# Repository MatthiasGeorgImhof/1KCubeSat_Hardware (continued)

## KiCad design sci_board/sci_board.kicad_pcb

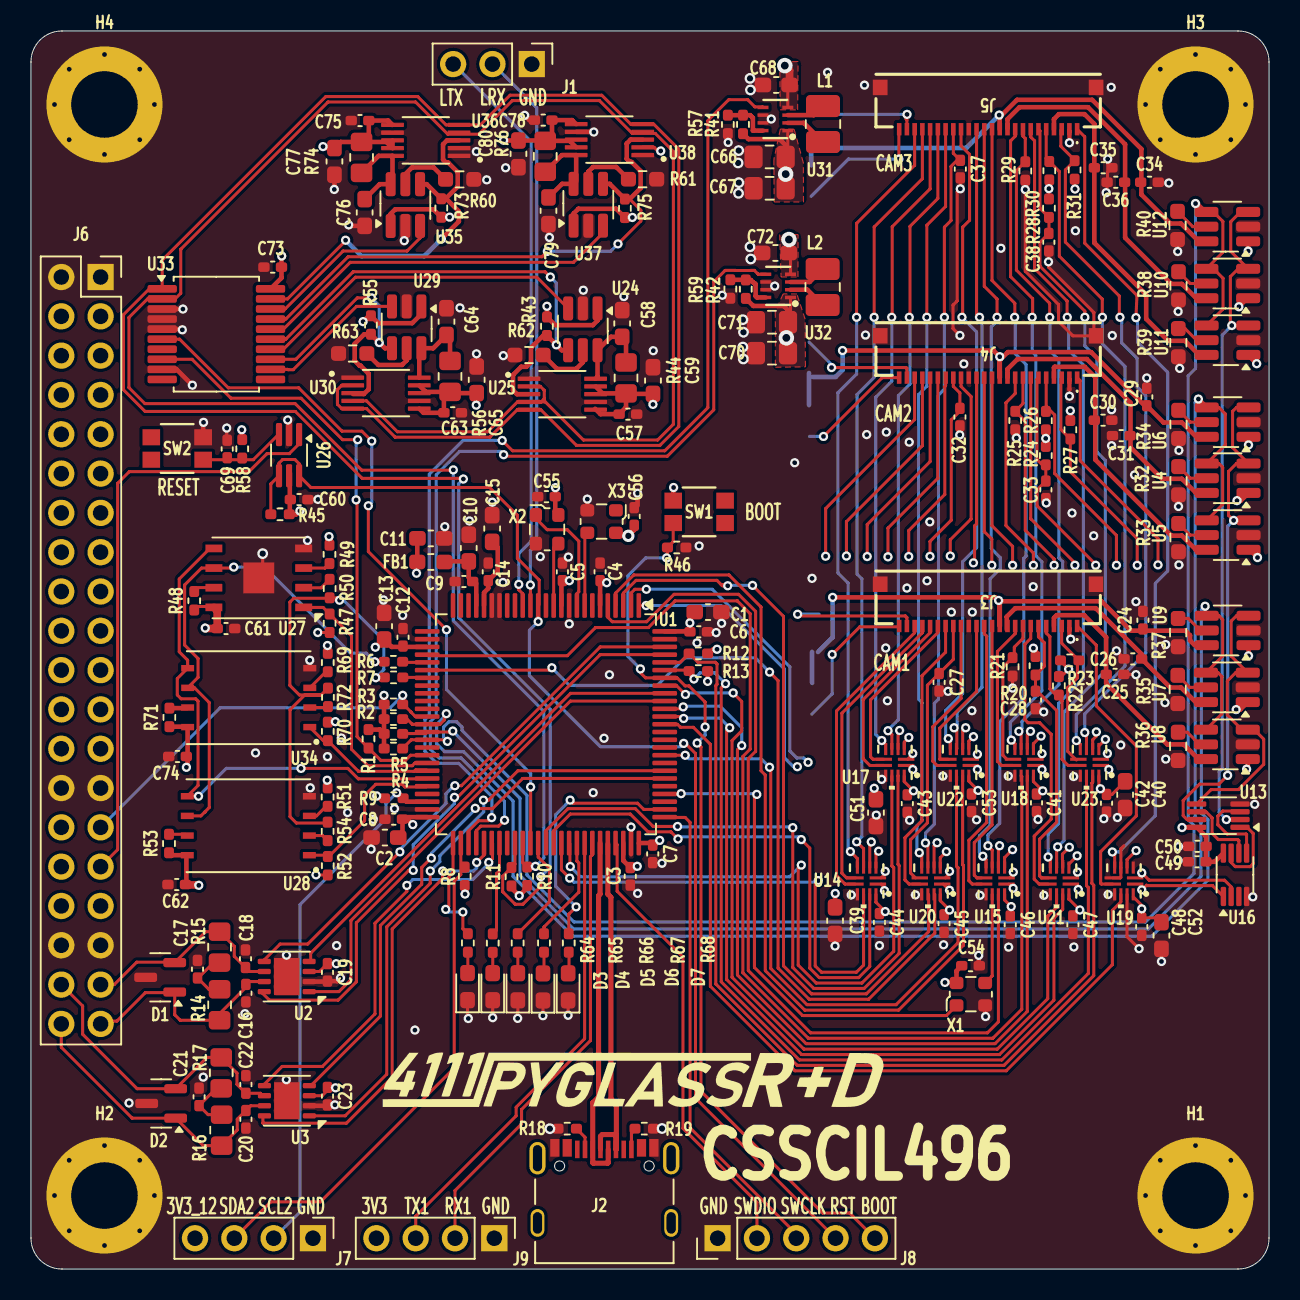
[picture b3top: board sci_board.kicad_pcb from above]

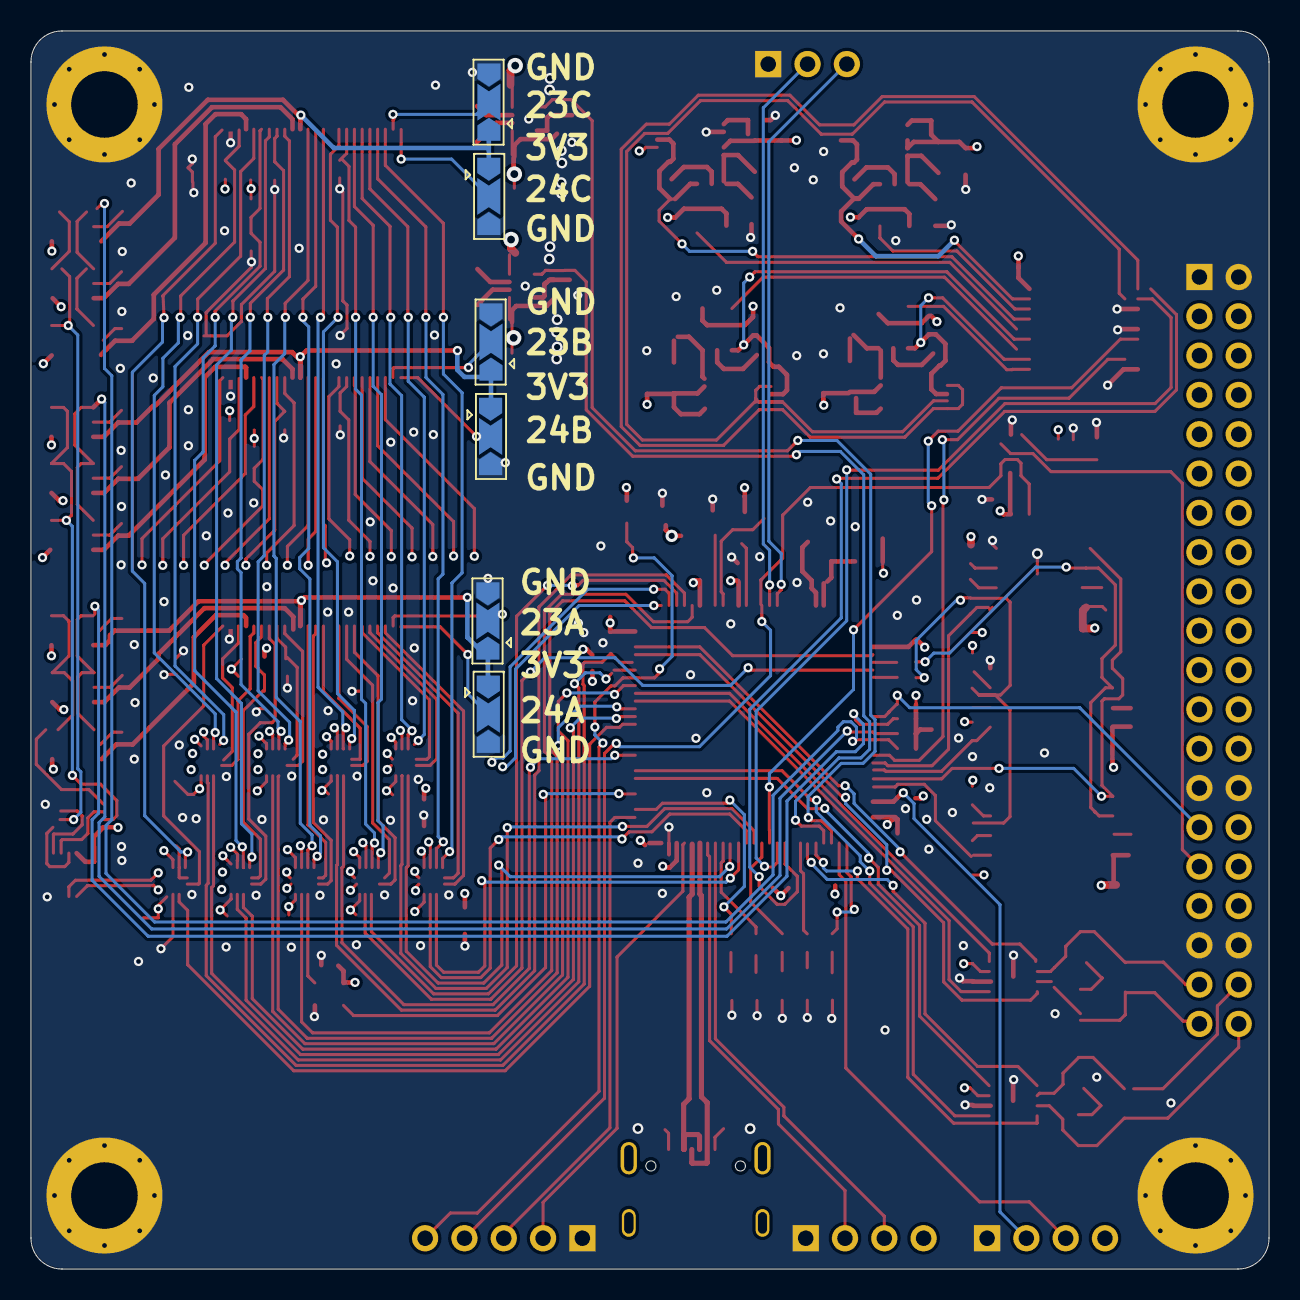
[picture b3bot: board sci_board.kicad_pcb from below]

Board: 4 copper layers, 80.0 x 80.0 mm, 231 parts (6 on the bottom side), 208 nets.

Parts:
C1, C2, C10, C11, C13, C15, C39, C40, C51, C52, C58, C59, C64, C65, C76, C77, C79, C80: 10uF; C_0603_1608Metric_Pad1.08x0.95mm_HandSolder
C3, C4, C5, C6, C7, C8, C9, C12, C14, C19, C23, C24, C25, C26, C28, C29, C30, C31, C33, C34, C35, C36, C38, C41, C42, C43, C44, C45, C46, C47, C48, C49, C50, C53, C54, C55, C56, C57, C60, C61, C62, C63, C69, C73, C74, C75, C78: 100nF; C_0402_1005Metric_Pad0.74x0.62mm_HandSolder
C16, C18, C20, C22: 100pF; C_0402_1005Metric_Pad0.74x0.62mm_HandSolder
C17, C21: 4.7nF; C_0402_1005Metric_Pad0.74x0.62mm_HandSolder
C27, C32, C37: 22pF; C_0402_1005Metric_Pad0.74x0.62mm_HandSolder
C66, C67, C70, C71: 47uF; C_0805_2012Metric_Pad1.18x1.45mm_HandSolder
C68, C72: 22uF; C_0603_1608Metric_Pad1.08x0.95mm_HandSolder
D1, D2: NUP2105LT1G; SOT-23
D3: LED_SMD_RED; LED_0603_1608Metric_Pad1.05x0.95mm_HandSolder
D4: LED_SMD_GREEN; LED_0603_1608Metric_Pad1.05x0.95mm_HandSolder
D5, D6, D7: LED_SMD_YELLOW; LED_0603_1608Metric_Pad1.05x0.95mm_HandSolder
FB1: 120R; L_0603_1608Metric_Pad1.05x0.95mm_HandSolder
H1, H2, H3, H4: MountingHole_Pad; MountingHole_4.3mm_M4_Pad_Via_Custom
J1: Conn_01x03_Pin; PinHeader_1x03_P2.54mm_Vertical
J2: 10155435-00011LF; AMPHENOL_10155435-00011LF
J3, J4, J5: 10051922-2410EHLF; 100519222410EHLF
J6: PC104 Conn_02x20_Odd_Even; PinSocket_2x20_P2.54mm_Vertical
J7: Conn_01x04_Pin; PinHeader_1x04_P2.54mm_Vertical
J8: Conn_01x06; PinHeader_1x05_P2.54mm_Vertical
J9: Conn_01x04; PinHeader_1x04_P2.54mm_Vertical
JP1, JP2, JP3, JP4, JP5, JP6: SolderJumper_3_Open; SolderJumper-3_P2.0mm_Open_TrianglePad1.0x1.5mm
L1, L2: 1uH; L_1008_2520Metric_Pad1.43x2.20mm_HandSolder
NT1, NT2, NT3: NetTie_2; NetTie-2_SMD_Pad0.3mm
R1, R2, R3, R4, R20, R21, R24, R25, R28, R29, R43, R45, R46, R47, R48, R49, R51, R52, R53, R55, R58, R69, R70, R71, R73, R75: 100K; R_0402_1005Metric_Pad0.72x0.64mm_HandSolder
R5: 330K; R_0402_1005Metric_Pad0.72x0.64mm_HandSolder
R6, R7, R50, R54, R72: 22R; R_0402_1005Metric_Pad0.72x0.64mm_HandSolder
R8, R9, R10, R11, R18, R19: 5K1; R_0402_1005Metric_Pad0.72x0.64mm_HandSolder
R12, R13, R22, R23, R26, R27, R30, R31: 10K; R_0402_1005Metric_Pad0.72x0.64mm_HandSolder
R14, R15, R16, R17: 60R4; R_0805_2012Metric_Pad1.20x1.40mm_HandSolder
R32, R33, R34, R35, R36, R37, R38, R39, R40, R60, R61, R62, R63: 988R; R_0603_1608Metric_Pad0.98x0.95mm_HandSolder
R41: 422K; R_0402_1005Metric_Pad0.72x0.64mm_HandSolder
R42: 182K; R_0402_1005Metric_Pad0.72x0.64mm_HandSolder
R44, R56, R74, R76: 10m; R_0805_2012Metric_Pad1.20x1.40mm_HandSolder
R57, R59: 91K; R_0402_1005Metric_Pad0.72x0.64mm_HandSolder
R64, R65, R66, R67, R68: 1K; R_0402_1005Metric_Pad0.72x0.64mm_HandSolder
SW1, SW2: EVP-AA602W; EVP602AA
U1: STM32L496VGTx; LQFP-100_14x14mm_P0.5mm
U2, U3: TCAN3414; VSON-8-1EP_3x3mm_P0.65mm_EP1.65x2.4mm
U4, U5, U6, U7, U8, U9, U10, U11, U12, U24, U29, U35, U37: MIC2009A-1YM6-TR; SOT-23-6_Handsoldering
U13: 74LVC3G04; VSSOP-8_2.3x2mm_P0.5mm
U14, U15, U17, U18, U19, U20, U21, U22, U23: TMUX131RMGR; VQFN12_RMG_TEX
U16: 74LVC1G139; VSSOP-8_2.3x2mm_P0.5mm
U25, U30, U36, U38: INA226AIDGSR; SOP50P490X110-10N
U26: 74LVC2G07; SOT-363_SC-70-6_Handsoldering
U27: MR25H10; DFN-8-1EP_6x5mm_P1.27mm_EP2x2mm
U28, U34: MT29F4G01ABAFDWB-IT:F TR; DFN800X600X65-8N
U31, U32: TPS631000DRLR; TPS631000DRLR_TEX
U33: MCP23008T-E/SS; SSOP-20_5.3x7.2mm_P0.65mm
X1: 24MHz; Oscillator_SMD_ECS_2520MV-xxx-xx-4Pin_2.5x2.0mm
X2: 10MHz; Oscillator_SMD_ECS_2520MV-xxx-xx-4Pin_2.5x2.0mm
X3: 32.768KHZ; Oscillator_SMD_ECS_2520MV-xxx-xx-4Pin_2.5x2.0mm

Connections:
+3V3_AUX: C73.1, J6.12, R43.1, R55.1, R73.1, R75.1, U24.1 (VIN), U29.1 (VIN), U33.20 (VDD), U35.1 (VIN), U37.1 (VIN), U38.2 (A0)
+3V3_STM32_Core: C1.2, C2.2, C3.1, C4.1, C5.1, C6.1, C7.1, C8.1, C11.1, C12.2, C13.2, C19.1, C23.1, C55.1, C56.1, C60.2, FB1.1, J6.17, J9.4, R1.1, R2.1, R3.1, R4.1, R5.1, R8.1, R9.1, R10.1, R11.1, R12.1, R13.1, R45.1, R58.1, SW1.1, U1.6 (VBAT), U1.11 (VDD), U1.28 (VDD), U1.50 (VDD), U1.73 (VDDUSB), U1.75 (VDD), U1.100 (VDD), U2.3 (VCC), U3.3 (VCC), U26.5 (VCC), X2.4 (VDD), X3.4 (VCC)
+BATT: C68.1, C72.1, J6.6, U31.4 (VIN), U32.4 (VIN)
/3V3_Cameras: C39.1, C40.1, C41.1, C42.1, C43.1, C44.1, C45.1, C46.1, C47.1, C48.1, C49.1, C50.1, C51.1, C52.1, C53.1, C54.1, C78.1, C80.1, R76.2, U6.1 (VIN), U9.1 (VIN), U12.1 (VIN), U13.8 (VCC), U14.12 (VDD), U15.12 (VDD), U16.8 (VCC), U17.12 (VDD), U18.12 (VDD), U19.12 (VDD), U20.12 (VDD), U21.12 (VDD), U22.12 (VDD), U23.12 (VDD), U38.6 (VS), U38.8 (VBUS), U38.9 (IN-), X1.4 (VDD)
/3V3_Flash: C57.1, C59.1, C62.1, C74.1, R44.2, R51.1, R52.1, R53.1, R69.1, R70.1, R71.1, U25.6 (VS), U25.8 (VBUS), U25.9 (IN-), U28.8 (VCC), U34.8 (VCC)
/3V3_Imager: C75.1, C77.1, J7.4, R74.2, U36.6 (VS), U36.8 (VBUS), U36.9 (IN-)
/3V3_MRAM: C61.1, C63.1, C65.1, R47.1, R48.1, R49.1, R56.2, U27.8 (VDD), U30.6 (VS), U30.8 (VBUS), U30.9 (IN-)
/ATTN: J6.29, R5.2, U1.37 (PB2)
/Aux Power Switch 3V3/ENABLE0: U33.18 (GP6), U35.3 (ENABLE)
/Aux Power Switch 3V3/ENABLE1: U33.16 (GP4), U37.3 (ENABLE)
/Aux Power Switch 3V3/ENABLE2: U24.3 (ENABLE), U33.14 (GP2)
/Aux Power Switch 3V3/ENABLE3: U29.3 (ENABLE), U33.12 (GP0)
/Aux Power Switch 3V3/INT0: R73.2, U33.19 (GP7), U35.4 (*FAULT), U36.3 (ALERT)
/Aux Power Switch 3V3/INT1: R75.2, U33.17 (GP5), U37.4 (*FAULT), U38.3 (ALERT)
/Aux Power Switch 3V3/INT2: R43.2, U24.4 (*FAULT), U25.3 (ALERT), U33.15 (GP3)
/Aux Power Switch 3V3/INT3: R55.2, U29.4 (*FAULT), U30.3 (ALERT), U33.13 (GP1)
/Aux Power Switch 3V3/RESET: U1.61 (PD14), U33.6 (*RESET)
/Aux Power Switch 3V3/SCL: R11.2, U1.59 (PD12), U25.5 (SCL), U30.2 (A0), U30.5 (SCL), U33.1 (SCL), U36.5 (SCL), U38.5 (SCL)
/Aux Power Switch 3V3/SDA: R10.2, U1.60 (PD13), U25.2 (A0), U25.4 (SDA), U30.4 (SDA), U33.2 (SDA), U36.4 (SDA), U38.4 (SDA)
/Aux Power Switch 3V3/sheet601A160D1/ILIMIT+: R60.1, U35.5 (ILIMIT)
/Aux Power Switch 3V3/sheet601A160D2/ILIMIT+: R61.1, U37.5 (ILIMIT)
/Aux Power Switch 3V3/sheet601A160D3/ILIMIT+: R62.1, U24.5 (ILIMIT)
/Aux Power Switch 3V3/sheet601A160D4/ILIMIT+: R63.1, U29.5 (ILIMIT)
/CAN1_H: C20.1, D2.1 (K), J6.40, R16.1, U3.7 (CANH)
/CAN1_L: C22.2, D2.2 (K), J6.38, R17.2, U3.6 (CANL)
/CAN1_RX: U1.81 (PD0), U3.4 (RXD)
/CAN1_SHDN: U1.56 (PD9), U3.5 (SHTD)
/CAN1_STB: U1.55 (PD8), U3.8 (STB)
/CAN1_TX: U1.82 (PD1), U3.1 (TXD)
/CAN2_H: C16.1, D1.1 (K), J6.39, R14.1, U2.7 (CANH)
/CAN2_L: C18.2, D1.2 (K), J6.37, R15.2, U2.6 (CANL)
/CAN2_RX: U1.92 (PB6), U2.4 (RXD)
/CAN2_SHDN: U1.98 (PE1), U2.5 (SHTD)
/CAN2_STB: U1.97 (PE0), U2.8 (STB)
/CAN2_TX: U1.91 (PB5), U2.1 (TXD)
/Cameras/1V5: C70.1, C71.1, R42.1, U4.1 (VIN), U7.1 (VIN), U10.1 (VIN), U32.1 (VOUT)
/Cameras/1V5_A: C26.1, J3.10, U7.6 (VOUT)
/Cameras/1V5_B: C31.1, J4.10, U4.6 (VOUT)
/Cameras/1V5_C: C36.1, J5.10, U10.6 (VOUT)
/Cameras/2V8: C66.1, C67.1, R41.1, U5.1 (VIN), U8.1 (VIN), U11.1 (VIN), U31.1 (VOUT)
/Cameras/2V8_A: C25.1, J3.4, U8.6 (VOUT)
/Cameras/2V8_B: C30.1, J4.4, U5.6 (VOUT)
/Cameras/2V8_C: C35.1, J5.4, U11.6 (VOUT)
/Cameras/3V3_A: C24.1, J3.11, JP1.1 (A), JP2.1 (A), R20.1, R22.1, R23.1, U9.6 (VOUT)
/Cameras/3V3_B: C29.1, J4.11, JP3.1 (A), JP4.1 (A), R24.1, R26.1, R27.1, U6.6 (VOUT)
/Cameras/3V3_C: C34.1, J5.11, JP5.1 (A), JP6.1 (A), R28.1, R30.1, R31.1, U12.6 (VOUT)
/Cameras/CLK_OE: U1.79 (PC11), X1.1 (TRI-STATE)
/Cameras/Camera_A/*RESET: C28.1, J3.6, R20.2, U21.7 (S1A)
/Cameras/Camera_A/A_GND: J3.2, NT1.1
/Cameras/Camera_A/DCMI_02: J3.19, U17.7 (S1A)
/Cameras/Camera_A/DCMI_03: J3.21, U14.7 (S1A)
/Cameras/Camera_A/DCMI_04: J3.22, U14.8 (S2A)
/Cameras/Camera_A/DCMI_05: J3.20, U17.8 (S2A)
/Cameras/Camera_A/DCMI_06: J3.18, U20.8 (S2A)
/Cameras/Camera_A/DCMI_07: J3.16, U22.8 (S2A)
/Cameras/Camera_A/DCMI_08: J3.14, U22.7 (S1A)
/Cameras/Camera_A/DCMI_09: J3.12, U15.7 (S1A)
/Cameras/Camera_A/DCMI_HSYNC: J3.9, U18.8 (S2A)
/Cameras/Camera_A/DCMI_PLXCLK: C27.1, J3.17, U20.7 (S1A)
/Cameras/Camera_A/DCMI_VSYNC: J3.7, U21.8 (S2A)
/Cameras/Camera_A/PWRDN: J3.8, R21.1, U18.7 (S1A)
/Cameras/Camera_A/SCK: J3.5, R22.2, U23.8 (S2A)
/Cameras/Camera_A/SDA: J3.3, R23.2, U23.7 (S1A)
/Cameras/Camera_A/STROBE: J3.1, U19.8 (S2A)
/Cameras/Camera_A/XCLK: J3.13, U15.8 (S2A)
/Cameras/Camera_B/*RESET: C33.1, J4.6, R24.2, U21.3 (S1B)
/Cameras/Camera_B/A_GND: J4.2, NT2.1
/Cameras/Camera_B/DCMI_02: J4.19, U17.3 (S1B)
/Cameras/Camera_B/DCMI_03: J4.21, U14.3 (S1B)
/Cameras/Camera_B/DCMI_04: J4.22, U14.4 (S2B)
/Cameras/Camera_B/DCMI_05: J4.20, U17.4 (S2B)
/Cameras/Camera_B/DCMI_06: J4.18, U20.4 (S2B)
/Cameras/Camera_B/DCMI_07: J4.16, U22.4 (S2B)
/Cameras/Camera_B/DCMI_08: J4.14, U22.3 (S1B)
/Cameras/Camera_B/DCMI_09: J4.12, U15.3 (S1B)
/Cameras/Camera_B/DCMI_HSYNC: J4.9, U18.4 (S2B)
/Cameras/Camera_B/DCMI_PLXCLK: C32.1, J4.17, U20.3 (S1B)
/Cameras/Camera_B/DCMI_VSYNC: J4.7, U21.4 (S2B)
/Cameras/Camera_B/PWRDN: J4.8, R25.1, U18.3 (S1B)
/Cameras/Camera_B/SCK: J4.5, R26.2, U23.4 (S2B)
/Cameras/Camera_B/SDA: J4.3, R27.2, U23.3 (S1B)
/Cameras/Camera_B/STROBE: J4.1, U19.4 (S2B)
/Cameras/Camera_B/XCLK: J4.13, U15.4 (S2B)
/Cameras/Camera_C/*RESET: C38.1, J5.6, R28.2, U21.5 (S1C)
/Cameras/Camera_C/A_GND: J5.2, NT3.1
/Cameras/Camera_C/DCMI_02: J5.19, U17.5 (S1C)
/Cameras/Camera_C/DCMI_03: J5.21, U14.5 (S1C)
/Cameras/Camera_C/DCMI_04: J5.22, U14.6 (S2C)
/Cameras/Camera_C/DCMI_05: J5.20, U17.6 (S2C)
/Cameras/Camera_C/DCMI_06: J5.18, U20.6 (S2C)
/Cameras/Camera_C/DCMI_07: J5.16, U22.6 (S2C)
/Cameras/Camera_C/DCMI_08: J5.14, U22.5 (S1C)
/Cameras/Camera_C/DCMI_09: J5.12, U15.5 (S1C)
/Cameras/Camera_C/DCMI_HSYNC: J5.9, U18.6 (S2C)
/Cameras/Camera_C/DCMI_PLXCLK: C37.1, J5.17, U20.5 (S1C)
/Cameras/Camera_C/DCMI_VSYNC: J5.7, U21.6 (S2C)
/Cameras/Camera_C/PWRDN: J5.8, R29.1, U18.5 (S1C)
/Cameras/Camera_C/SCK: J5.5, R30.2, U23.6 (S2C)
/Cameras/Camera_C/SDA: J5.3, R31.2, U23.5 (S1C)
/Cameras/Camera_C/STROBE: J5.1, U19.6 (S2C)
/Cameras/Camera_C/XCLK: J5.13, U15.6 (S2C)
/Cameras/DCMI_00: U1.63 (PC6), U17.11 (D1)
/Cameras/DCMI_01: U1.64 (PC7), U14.11 (D1)
/Cameras/DCMI_02: U1.65 (PC8), U14.10 (D2)
/Cameras/DCMI_03: U1.66 (PC9), U17.10 (D2)
/Cameras/DCMI_04: U1.3 (PE4), U20.10 (D2)
/Cameras/DCMI_05: U1.84 (PD3), U22.10 (D2)
/Cameras/DCMI_06: U1.4 (PE5), U22.11 (D1)
/Cameras/DCMI_07: U1.5 (PE6), U15.11 (D1)
/Cameras/DCMI_HSYNC: U1.29 (PA4), U18.10 (D2)
/Cameras/DCMI_PLXCLK: U1.31 (PA6), U20.11 (D1)
/Cameras/DCMI_VSYNC: U1.93 (PB7), U21.10 (D2)
/Cameras/EN_1V5: U1.54 (PB15), U32.5 (EN)
/Cameras/EN_2V8: U1.53 (PB14), U31.5 (EN)
/Cameras/I2C_SCK: R13.2, U1.95 (PB8), U23.10 (D2)
/Cameras/I2C_SDA: R12.2, U1.96 (PB9), U23.11 (D1)
/Cameras/Multiplexer/EN_A: U7.3 (ENABLE), U8.3 (ENABLE), U9.3 (ENABLE), U13.5
/Cameras/Multiplexer/EN_B: U4.3 (ENABLE), U5.3 (ENABLE), U6.3 (ENABLE), U13.7
/Cameras/Multiplexer/EN_C: U10.3 (ENABLE), U11.3 (ENABLE), U12.3 (ENABLE), U13.2
/Cameras/PWRDN: U1.90 (PB4), U18.11 (D1)
/Cameras/Power Regulator MP3416/LX1: L1.2, U31.3 (LX1)
/Cameras/Power Regulator MP3416/LX2: L1.1, U31.2 (LX2)
/Cameras/Power Regulator MP3416/R-: R41.2, R57.1, U31.8 (FB)
/Cameras/Power Regulator MP3417/LX1: L2.2, U32.3 (LX1)
/Cameras/Power Regulator MP3417/LX2: L2.1, U32.2 (LX2)
/Cameras/Power Regulator MP3417/R-: R42.2, R59.1, U32.8 (FB)
/Cameras/RESET: U1.89 (PB3), U21.11 (D1)
/Cameras/S0: U1.1 (PE2), U14.1 (SEL0), U15.1 (SEL0), U16.1 (A), U17.1 (SEL0), U18.1 (SEL0), U19.1 (SEL0), U20.1 (SEL0), U21.1 (SEL0), U22.1 (SEL0), U23.1 (SEL0)
/Cameras/S1: U1.2 (PE3), U14.2 (SEL1), U15.2 (SEL1), U16.2 (B), U17.2 (SEL1), U18.2 (SEL1), U19.2 (SEL1), U20.2 (SEL1), U21.2 (SEL1), U22.2 (SEL1), U23.2 (SEL1)
/Cameras/STROBE: U1.88 (PD7), U19.10 (D2)
/Cameras/XCLK: U15.10 (D2), X1.3 (OUTPUT)
/Flash1/SPI_CLK: R6.2, U27.6 (SCK), U28.6 (SCK), U34.6 (SCK)
/Flash1/SPI_CS: R52.2, U1.46 (PE15), U28.1 (CS#)
/Flash1/SPI_MISO: R7.2, R50.2, R54.1, R72.1
/Flash1/SPI_MOSI: U1.45 (PE14), U27.5 (SI), U28.5 (SI/IO0), U34.5 (SI/IO0)
/Flash2/SPI_CS: R70.2, U1.44 (PE13), U34.1 (CS#)
/INT1: R2.2, U1.38 (PE7), U7.4 (*FAULT), U8.4 (*FAULT), U9.4 (*FAULT)
/INT2: R3.2, U1.39 (PE8), U4.4 (*FAULT), U5.4 (*FAULT), U6.4 (*FAULT)
/INT3: R4.2, U1.40 (PE9), U10.4 (*FAULT), U11.4 (*FAULT), U12.4 (*FAULT)
/MRAM/SPI_CS: R47.2, U1.43 (PE12), U27.1 (~CS)
/PMIC/BOOT0: J8.5, R46.1, SW1.2, U1.94 (PH3)
/PMIC/I2C2_SCK: J7.2, R9.2, U1.48 (PB11)
/PMIC/I2C2_SDA: J7.3, R8.2, U1.52 (PB13)
/PMIC/LED1: R64.1, U1.51 (PB12)
/PMIC/LED2: R65.1, U1.57 (PD10)
/PMIC/LED3: R66.1, U1.62 (PD15)
/PMIC/LED4: R67.1, U1.67 (PA8)
/PMIC/LED5: R68.1, U1.77 (PA15)
/PMIC/LPUART_RX: J1.2, U1.15 (PC0)
/PMIC/LPUART_TX: J1.3, U1.16 (PC1)
/PMIC/OSC32_TCXO/OUT: U1.8 (PC14), X3.3 (OUT)
/PMIC/OSC_HSE_OE: U1.9 (PC15), X2.1 (TRI-STATE)
/PMIC/OSC_HSE_TCXO/OUT: U1.12 (PH0), X2.3 (OUTPUT)
/PMIC/RESET: J8.4, R45.2, U1.14 (NRST), U26.4 (OUT2), U26.6 (OUT1)
/PMIC/RESET/RESET: C69.1, R58.2, SW2.3, U26.3 (IN2)
/PMIC/SWCLK: J8.3, U1.76 (PA14)
/PMIC/SWDIO: J8.2, U1.72 (PA13)
/PMIC/USART1_RX: J9.2, U1.69 (PA10)
/PMIC/USART1_TX: J9.3, U1.68 (PA9)
/PMIC/USB_OTG_FS_DM: J2.A7 (DN1_A), J2.B7 (DN2_B), U1.70 (PA11)
/PMIC/USB_OTG_FS_DP: J2.A6 (DP1_A), J2.B6 (DP2_B), U1.71 (PA12)
/Power_INT: R1.2, U1.42 (PE11), U33.8 (INT)
/RESET: J6.31, U26.1 (IN1)
GND: C1.1, C2.1, C3.2, C4.2, C5.2, C6.2, C7.2, C8.2, C9.2, C10.2, C11.2, C12.1, C13.1, C14.1, C15.1, C16.2, C17.2, C18.1, C19.2, C20.2, C21.2, C22.1, C23.2, C24.2, C25.2, C26.2, C27.2, C28.2, C29.2, C30.2, C31.2, C32.2, C33.2, C34.2, C35.2, C36.2, C37.2, C38.2, C39.2, C40.2, C41.2, C42.2, C43.2, C44.2, C45.2, C46.2, C47.2, C48.2, C49.2, C50.2, C51.2, C52.2, C53.2, C54.2, C55.2, C56.2, C57.2, C58.2, C59.2, C60.1, C61.2, C62.2, C63.2, C64.2, C65.2, C66.2, C67.2, C68.2, C69.2, C70.2, C71.2, C72.2, C73.2, C74.2, C75.2, C76.2, C77.2, C78.2, C79.2, C80.2, D1.3 (A), D2.3 (A), D3.1 (K), D4.1 (K), D5.1 (K), D6.1 (K), D7.1 (K), H1.1, H2.1, H3.1, H4.1, J1.1, J2.A1_B12 (GND), J2.B1_A12 (GND__1), J3.15, J3.MP1, J3.MP2, J4.15, J4.MP1, J4.MP2, J5.15, J5.MP1, J5.MP2, J6.1, J6.2, J6.27, J6.28, J6.35, J6.36, J7.1, J8.1, J9.1, JP1.3 (B), JP2.3 (B), JP3.3 (B), JP4.3 (B), JP5.3 (B), JP6.3 (B), NT1.2, NT2.2, NT3.2, R18.1, R19.1, R21.2, R25.2, R29.2, R32.2, R33.2, R34.2, R35.2, R36.2, R37.2, R38.2, R39.2, R40.2, R46.2, R57.2, R59.2, R60.2, R61.2, R62.2, R63.2, SW2.4, U1.10 (VSS), U1.19 (VSSA), U1.20 (VREF-), U1.27 (VSS), U1.49 (VSS), U1.74 (VSS), U1.99 (VSS), U2.2 (GND), U2.9 (GND), U3.2 (GND), U3.9 (GND), U4.2 (GND), U5.2 (GND), U6.2 (GND), U7.2 (GND), U8.2 (GND), U9.2 (GND), U10.2 (GND), U11.2 (GND), U12.2 (GND), U13.4 (GND), U14.9 (GND), U15.9 (GND), U16.4 (GND), U17.9 (GND), U18.9 (GND), U19.3 (S1B), U19.5 (S1C), U19.7 (S1A), U19.9 (GND), U19.11 (D1), U20.9 (GND), U21.9 (GND), U22.9 (GND), U23.9 (GND), U24.2 (GND), U25.1 (A1), U25.7 (GND), U26.2 (GND), U27.4 (VSS), U27.9 (PAD), U28.4 (VSS), U29.2 (GND), U30.1 (A1), U30.7 (GND), U31.6 (MODE), U31.7 (GND), U32.6 (MODE), U32.7 (GND), U33.3 (A2), U33.4 (A1), U33.5 (A0), U33.9 (VSS), U34.4 (VSS), U35.2 (GND), U36.1 (A1), U36.2 (A0), U36.7 (GND), U37.2 (GND), U38.1 (A1), U38.7 (GND), X1.2 (GND), X2.2 (GND), X3.2 (GND)
unnamed: C17.1, R14.2, R15.1
unnamed: C21.1, R16.2, R17.1
unnamed: D3.2 (A), R64.2
unnamed: D4.2 (A), R65.2
unnamed: D5.2 (A), R66.2
unnamed: D6.2 (A), R67.2
unnamed: D7.2 (A), R68.2
unnamed: J2.A5 (CC1_A), R18.2
unnamed: J2.B5 (CC2_B), R19.2
unnamed: J3.23, JP1.2 (C)
unnamed: J3.24, JP2.2 (C)
unnamed: J4.23, JP3.2 (C)
unnamed: J4.24, JP4.2 (C)
unnamed: J5.23, JP5.2 (C)
unnamed: J5.24, JP6.2 (C)
unnamed: R6.1, U1.30 (PA5)
unnamed: R7.1, U1.32 (PA7)
unnamed: C9.1, C10.1, FB1.2, U1.22 (VDDA)
unnamed: C14.2, C15.2, U1.21 (VREF+)
unnamed: R32.1, U4.5 (ILIMIT)
unnamed: R33.1, U5.5 (ILIMIT)
unnamed: R34.1, U6.5 (ILIMIT)
unnamed: R35.1, U7.5 (ILIMIT)
unnamed: R36.1, U8.5 (ILIMIT)
unnamed: R37.1, U9.5 (ILIMIT)
unnamed: R38.1, U10.5 (ILIMIT)
unnamed: R39.1, U11.5 (ILIMIT)
unnamed: R40.1, U12.5 (ILIMIT)
unnamed: U13.1, U16.7 (Y0)
unnamed: U13.6, U16.6 (Y1)
unnamed: U13.3, U16.5 (Y2)
unnamed: C58.1, R44.1, U24.6 (VOUT), U25.10 (IN+)
unnamed: R50.1, U27.2 (SO)
unnamed: R48.2, U27.7 (~HOLD)
unnamed: R49.2, U27.3 (~WP)
unnamed: R53.2, U28.7 (HOLD#/IO3)
unnamed: R54.2, U28.2 (SO/IO1)
unnamed: R51.2, U28.3 (WP#/IO2)
unnamed: C64.1, R56.1, U29.6 (VOUT), U30.10 (IN+)
unnamed: R71.2, U34.7 (HOLD#/IO3)
unnamed: R72.2, U34.2 (SO/IO1)
unnamed: R69.2, U34.3 (WP#/IO2)
unnamed: C76.1, R74.1, U35.6 (VOUT), U36.10 (IN+)
unnamed: C79.1, R76.1, U37.6 (VOUT), U38.10 (IN+)

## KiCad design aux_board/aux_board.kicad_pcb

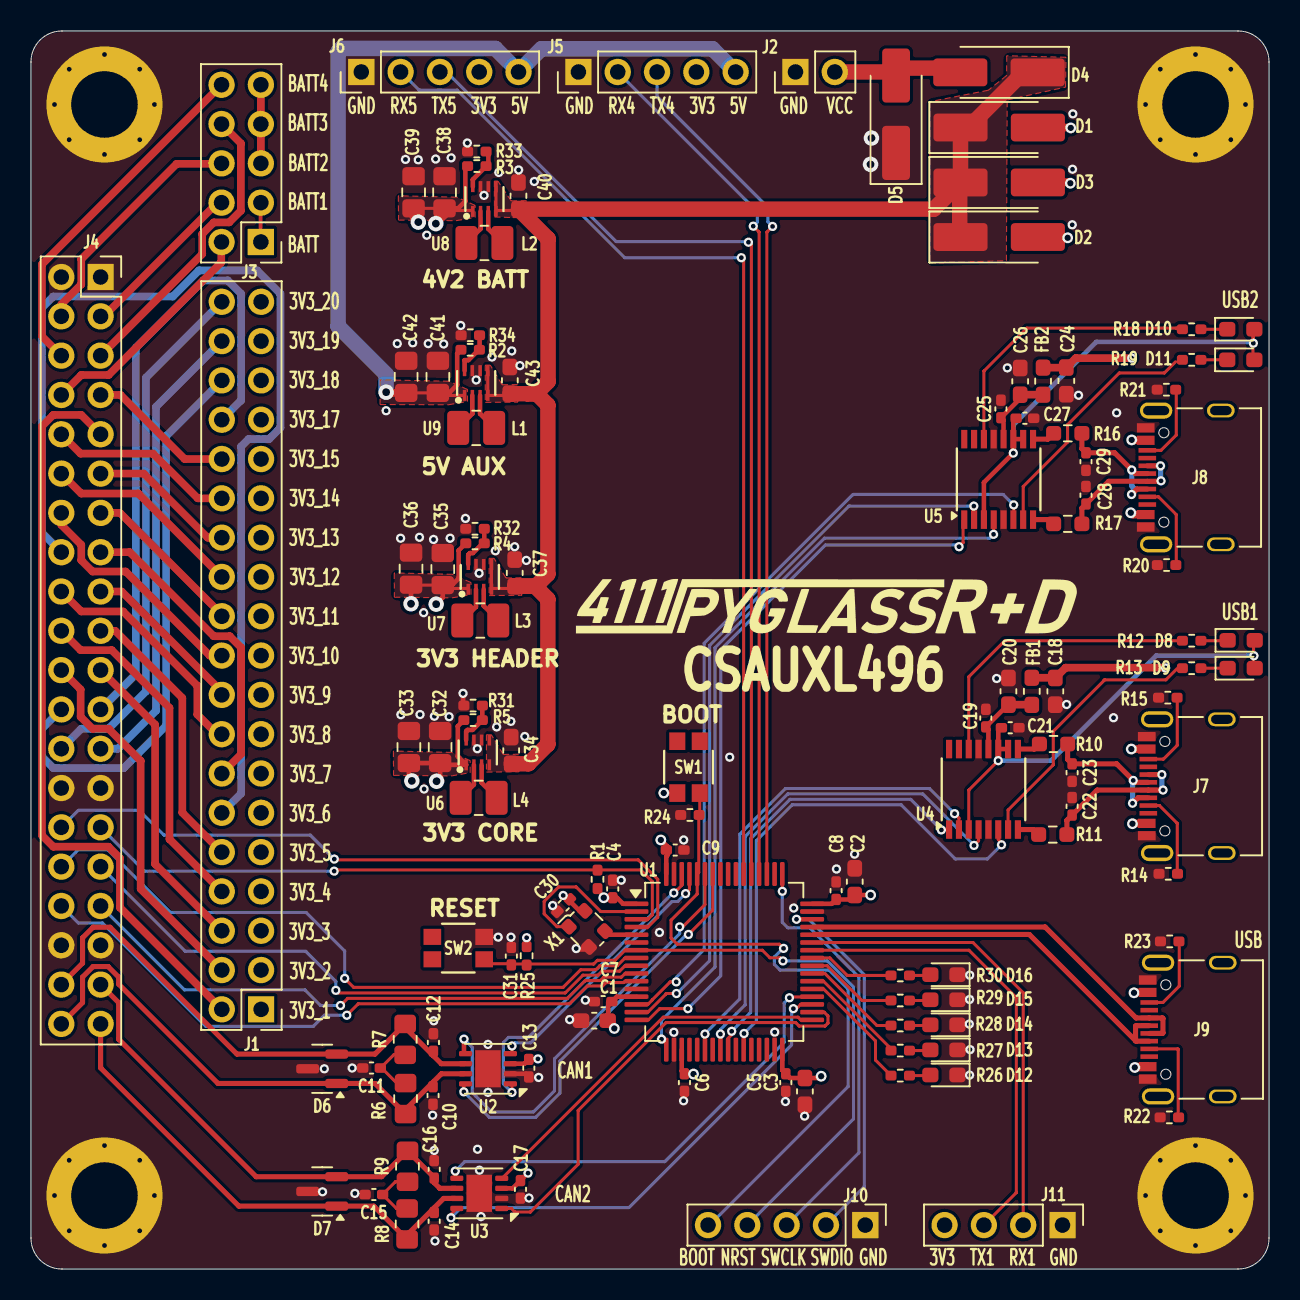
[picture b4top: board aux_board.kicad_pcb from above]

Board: 4 copper layers, 80.0 x 80.0 mm, 126 parts (0 on the bottom side), 124 nets.

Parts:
C1, C2, C3, C18, C20, C24, C26: 10uF; C_0603_1608Metric_Pad1.08x0.95mm_HandSolder
C4, C5, C6, C7, C8, C9, C13, C17, C19, C21, C25, C27, C30, C31: 100nF; C_0402_1005Metric_Pad0.74x0.62mm_HandSolder
C10, C12, C14, C16: 100pF; C_0402_1005Metric_Pad0.74x0.62mm_HandSolder
C11, C15: 4.7nF; C_0402_1005Metric_Pad0.74x0.62mm_HandSolder
C22, C23, C28, C29: 47pF; C_0402_1005Metric_Pad0.74x0.62mm_HandSolder
C32, C33, C35, C36, C38, C39, C41, C42: 47uF; C_0805_2012Metric_Pad1.18x1.45mm_HandSolder
C34, C37, C40, C43: 22uF; C_0603_1608Metric_Pad1.08x0.95mm_HandSolder
D1, D2, D3, D4: CDBA240LL-HF; D_SMA_Handsoldering
D5: SMAJ5.0A; D_SMA_Handsoldering
D6, D7: NUP2105LT1G; SOT-23
D8, D10, D13: LED_SMD_GREEN; LED_0603_1608Metric_Pad1.05x0.95mm_HandSolder
D9, D11, D12: LED_SMD_RED; LED_0603_1608Metric_Pad1.05x0.95mm_HandSolder
D14, D15, D16: LED_SMD_YELLOW; LED_0603_1608Metric_Pad1.05x0.95mm_HandSolder
FB1, FB2: 120R; L_0603_1608Metric_Pad1.05x0.95mm_HandSolder
H1, H2, H3, H4: MountingHole_Pad; MountingHole_4.3mm_M4_Pad_Via_Custom
J1: Conn_02x19_Odd_Even; PinHeader_2x19_P2.54mm_Vertical
J2: Conn_01x02_Pin; PinHeader_1x02_P2.54mm_Vertical
J3: Conn_02x05_Odd_Even; PinHeader_2x05_P2.54mm_Vertical
J4: PC104 Conn_02x20_Odd_Even; PinSocket_2x20_P2.54mm_Vertical
J5, J6: Conn_01x05_Pin; PinHeader_1x05_P2.54mm_Vertical
J7, J8, J9: 10155435-00011LF; AMPHENOL_10155435-00011LF
J10: Conn_01x06; PinHeader_1x05_P2.54mm_Vertical
J11: Conn_01x04; PinHeader_1x04_P2.54mm_Vertical
L1, L2, L3, L4: 1uH; L_1008_2520Metric_Pad1.43x2.20mm_HandSolder
R1: 330K; R_0402_1005Metric_Pad0.72x0.64mm_HandSolder
R2: 806K; R_0402_1005Metric_Pad0.72x0.64mm_HandSolder
R3: 665K; R_0402_1005Metric_Pad0.72x0.64mm_HandSolder
R4, R5: 511K; R_0402_1005Metric_Pad0.72x0.64mm_HandSolder
R6, R7, R8, R9: 60R4; R_0805_2012Metric_Pad1.20x1.40mm_HandSolder
R10, R11, R16, R17: 27R; R_0603_1608Metric_Pad0.98x0.95mm_HandSolder
R12, R13, R18, R19, R26, R27, R28, R29, R30: 1K; R_0402_1005Metric_Pad0.72x0.64mm_HandSolder
R14, R15, R20, R21, R22, R23: 5K1; R_0402_1005Metric_Pad0.72x0.64mm_HandSolder
R24, R25: 100K; R_0402_1005Metric_Pad0.72x0.64mm_HandSolder
R31, R32, R33, R34: 91K; R_0402_1005Metric_Pad0.72x0.64mm_HandSolder
SW1, SW2: EVP-AA602W; EVP602AA
U1: STM32L496RGT6; LQFP-64_10x10mm_P0.5mm
U2, U3: TCAN3414; VSON-8-1EP_3x3mm_P0.65mm_EP1.65x2.4mm
U4, U5: FT230XS; SSOP-16_3.9x4.9mm_P0.635mm
U6, U7, U8, U9: TPS631000DRLR; TPS631000DRLR_TEX
X1: 10MHz; Oscillator_SMD_ECS_2520MV-xxx-xx-4Pin_2.5x2.0mm

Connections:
+3V3: C35.1, C36.1, J1.1, J1.3, J1.5, J1.7, J1.9, J1.11, J1.13, J1.15, J1.17, J1.19, J1.21, J1.23, J1.25, J1.27, J1.29, J1.31, J1.33, J1.35, J1.37, R4.2, U7.1 (VOUT)
+3V3_Core: C1.1, C2.1, C3.1, C4.1, C5.1, C6.1, C7.1, C8.1, C9.1, C13.1, C17.1, C30.1, C32.1, C33.1, J5.4, J6.4, J11.4, R1.1, R5.2, R25.1, SW1.1, U1.1 (VBAT), U1.13 (VDDA), U1.19 (VDD), U1.32 (VDD), U1.48 (VDDUSB), U1.64 (VDD), U2.3 (VCC), U3.3 (VCC), U6.1 (VOUT), X1.4 (VDD)
+5V: C41.1, C42.1, J5.5, J6.5, R2.2, U9.1 (VOUT)
+VBAT: C38.1, C39.1, J3.1, J3.3, J3.5, J3.7, J3.9, R3.2, U8.1 (VOUT)
/*ATTENTION: J4.29, R1.2, U1.3 (PC14)
/*AVI_RST: J4.32, U1.8 (PC0)
/*COMM1_RST: J4.33, U1.10 (PC2)
/*COMM2_RST: J4.34, U1.11 (PC3)
/*EPS_RST: J4.30, U1.4 (PC15)
/*SCI_RST: J4.31, U1.9 (PC1)
/CAN1_H: C10.1, D6.1 (K), J4.40, R6.1, U2.7 (CANH)
/CAN1_L: C12.2, D6.2 (K), J4.38, R7.2, U2.6 (CANL)
/CAN2_H: C14.1, D7.1 (K), J4.39, R8.1, U3.7 (CANH)
/CAN2_L: C16.2, D7.2 (K), J4.37, R9.2, U3.6 (CANL)
/CAN TO USB/BOOT: J10.5, R24.1, SW1.2, U1.60 (PH3_BOOT0)
/CAN TO USB/CAN1_RX: U1.61 (PB8), U2.4 (RXD)
/CAN TO USB/CAN1_SHTD: U1.59 (PB7), U2.5 (SHTD)
/CAN TO USB/CAN1_STB: U1.58 (PB6), U2.8 (STB)
/CAN TO USB/CAN1_TX: U1.62 (PB9), U2.1 (TXD)
/CAN TO USB/CAN2_RX: U1.33 (PB12), U3.4 (RXD)
/CAN TO USB/CAN2_SHTD: U1.36 (PB15), U3.5 (SHTD)
/CAN TO USB/CAN2_STB: U1.35 (PB14), U3.8 (STB)
/CAN TO USB/CAN2_TX: U1.34 (PB13), U3.1 (TXD)
/CAN TO USB/FTDI1/3V3: C27.1, D10.2 (A), D11.2 (A), U5.3 (VCCIO), U5.10 (3V3OUT), U5.11 (~RESET)
/CAN TO USB/FTDI1/RXLED: R19.2, U5.7 (CBUS2)
/CAN TO USB/FTDI1/TXLED: R18.2, U5.14 (CBUS1)
/CAN TO USB/FTDI1/USB/DN: C29.1, J8.A7 (DN1_A), J8.B7 (DN2_B), R16.1
/CAN TO USB/FTDI1/USB/DP: C28.1, J8.A6 (DP1_A), J8.B6 (DP2_B), R17.1
/CAN TO USB/FTDI/3V3: C21.1, D8.2 (A), D9.2 (A), U4.3 (VCCIO), U4.10 (3V3OUT), U4.11 (~RESET)
/CAN TO USB/FTDI/RXLED: R13.2, U4.7 (CBUS2)
/CAN TO USB/FTDI/TXLED: R12.2, U4.14 (CBUS1)
/CAN TO USB/FTDI/USB/DN: C23.1, J7.A7 (DN1_A), J7.B7 (DN2_B), R10.1
/CAN TO USB/FTDI/USB/DP: C22.1, J7.A6 (DP1_A), J7.B6 (DP2_B), R11.1
/CAN TO USB/HSE_IN: U1.5 (PH0), X1.3 (OUTPUT)
/CAN TO USB/LED1: R26.1, U1.37 (PC6)
/CAN TO USB/LED2: R27.1, U1.38 (PC7)
/CAN TO USB/LED3: R28.1, U1.39 (PC8)
/CAN TO USB/LED4: R29.1, U1.40 (PC9)
/CAN TO USB/LED5: R30.1, U1.41 (PA8)
/CAN TO USB/NRST: C31.1, J10.4, R25.2, SW2.3, U1.7 (NRST)
/CAN TO USB/OSC_HSE_OE: U1.2 (PC13), X1.1 (TRI-STATE)
/CAN TO USB/SYS_JTMS_SWCLK: J10.3, U1.49 (PA14)
/CAN TO USB/SYS_JTMS_SWDIO: J10.2, U1.46 (PA13)
/CAN TO USB/UART4_RX: J5.2, U1.52 (PC11)
/CAN TO USB/UART4_TX: J5.3, U1.51 (PC10)
/CAN TO USB/UART5_RX: J6.2, U1.54 (PD2)
/CAN TO USB/UART5_TX: J6.3, U1.53 (PC12)
/CAN TO USB/USART1_RX: J11.2, U1.43 (PA10)
/CAN TO USB/USART1_TX: J11.3, U1.42 (PA9)
/CAN TO USB/USART2_CTS: U1.14 (PA0), U5.6 (~CTS)
/CAN TO USB/USART2_RTS: U1.15 (PA1), U5.2 (~RTS)
/CAN TO USB/USART2_RX: U1.17 (PA3), U5.4 (RXD)
/CAN TO USB/USART2_TX: U1.16 (PA2), U5.1 (TXD)
/CAN TO USB/USART3_CTS: U1.22 (PA6), U4.2 (~RTS)
/CAN TO USB/USART3_RTS: U1.27 (PB1), U4.6 (~CTS)
/CAN TO USB/USART3_RX: U1.25 (PC5), U4.1 (TXD)
/CAN TO USB/USART3_TX: U1.24 (PC4), U4.4 (RXD)
/CAN TO USB/USB_OTG_FS_D+: J9.A6 (DP1_A), J9.B6 (DP2_B), U1.45 (PA12)
/CAN TO USB/USB_OTG_FS_D-: J9.A7 (DN1_A), J9.B7 (DN2_B), U1.44 (PA11)
/CAN TO USB/VBUS1: D1.2 (A), J9.A4_B9 (VBUS), J9.B4_A9 (VBUS__1)
/CAN TO USB/VBUS2: C24.1, D2.2 (A), FB2.1, J8.A4_B9 (VBUS), J8.B4_A9 (VBUS__1)
/CAN TO USB/VBUS3: C18.1, D3.2 (A), FB1.1, J7.A4_B9 (VBUS), J7.B4_A9 (VBUS__1)
/INTERBOARD_CONNECTOR/3V3_1_AVI_STM_CORE: J1.2, J4.9
/INTERBOARD_CONNECTOR/3V3_2_AVI_GPS: J1.4, J4.22
/INTERBOARD_CONNECTOR/3V3_3_AVI_MRAM: J1.6, J4.21
/INTERBOARD_CONNECTOR/3V3_4_AVI_SUN: J1.8, J4.20
/INTERBOARD_CONNECTOR/3V3_5_AVI_ACS_LOGIC: J1.10, J4.19
/INTERBOARD_CONNECTOR/3V3_6_AVI_GYRO: J1.12, J4.16
/INTERBOARD_CONNECTOR/3V3_7_AVI_MAG: J1.14, J4.15
/INTERBOARD_CONNECTOR/3V3_8_AVI_CLK: J1.16, J4.18
/INTERBOARD_CONNECTOR/3V3_9_SCI_STM_CORE: J1.18, J4.17
/INTERBOARD_CONNECTOR/3V3_10_SCI_MRAM: J1.20, J4.14
/INTERBOARD_CONNECTOR/3V3_11_SCI_FLASH: J1.22, J4.13
/INTERBOARD_CONNECTOR/3V3_12_SCI_THERMAL: J1.24, J4.12
/INTERBOARD_CONNECTOR/3V3_13_SCI_CAMERAS: J1.26, J4.11
/INTERBOARD_CONNECTOR/3V3_14_EXTRA1: J1.28, J4.10
/INTERBOARD_CONNECTOR/3V3_15_EXTRA2: J1.30, J4.7
/INTERBOARD_CONNECTOR/3V3_17_RF1_BRIDGE: J1.32, J4.23
/INTERBOARD_CONNECTOR/3V3_18_RF1_COMM: J1.34, J4.24
/INTERBOARD_CONNECTOR/3V3_19_RF2_BRIDGE: J1.36, J4.25
/INTERBOARD_CONNECTOR/3V3_20_RF2_COMM: J1.38, J4.26
/INTERBOARD_CONNECTOR/BATT: J3.2, J4.8
/INTERBOARD_CONNECTOR/BATT_1_COMM1_VRF: J3.4, J4.3
/INTERBOARD_CONNECTOR/BATT_2_COMM2_VRF: J3.6, J4.4
/INTERBOARD_CONNECTOR/BATT_3_AVI_ACS_COIL: J3.8, J4.5
/INTERBOARD_CONNECTOR/BATT_4_SCI_CAMERAS: J3.10, J4.6
/Regulator 3V3/LX1: L3.1, U7.3 (LX1)
/Regulator 3V3/LX2: L3.2, U7.2 (LX2)
/Regulator 3V3/R-: R4.1, R32.1, U7.8 (FB)
/Regulator 3V4/LX1: L4.1, U6.3 (LX1)
/Regulator 3V4/LX2: L4.2, U6.2 (LX2)
/Regulator 3V4/R-: R5.1, R31.1, U6.8 (FB)
/Regulator 4V2/LX1: L2.1, U8.3 (LX1)
/Regulator 4V2/LX2: L2.2, U8.2 (LX2)
/Regulator 4V2/R-: R3.1, R33.1, U8.8 (FB)
/Regulator 5V/LX1: L1.1, U9.3 (LX1)
/Regulator 5V/LX2: L1.2, U9.2 (LX2)
/Regulator 5V/R-: R2.1, R34.1, U9.8 (FB)
GND: C1.2, C2.2, C3.2, C4.2, C5.2, C6.2, C7.2, C8.2, C9.2, C10.2, C11.2, C12.1, C13.2, C14.2, C15.2, C16.1, C17.2, C18.2, C19.2, C20.2, C21.2, C22.2, C23.2, C24.2, C25.2, C26.2, C27.2, C28.2, C29.2, C30.2, C31.2, C32.2, C33.2, C34.2, C35.2, C36.2, C37.2, C38.2, C39.2, C40.2, C41.2, C42.2, C43.2, D5.1 (A1), D6.3 (A), D7.3 (A), D12.1 (K), D13.1 (K), D14.1 (K), D15.1 (K), D16.1 (K), H1.1, H2.1, H3.1, H4.1, J2.1, J4.1, J4.2, J4.27, J4.28, J4.35, J4.36, J5.1, J6.1, J7.A1_B12 (GND), J7.B1_A12 (GND__1), J8.A1_B12 (GND), J8.B1_A12 (GND__1), J9.A1_B12 (GND), J9.B1_A12 (GND__1), J10.1, J11.1, R14.1, R15.1, R20.1, R21.1, R22.1, R23.1, R24.2, R31.2, R32.2, R33.2, R34.2, SW2.4, U1.12 (VSSA), U1.18 (VSS), U1.31 (VSS), U1.47 (VSS), U1.63 (VSS), U2.2 (GND), U2.9 (GND), U3.2 (GND), U3.9 (GND), U4.5 (GND), U4.13 (GND), U5.5 (GND), U5.13 (GND), U6.6 (MODE), U6.7 (GND), U7.6 (MODE), U7.7 (GND), U8.6 (MODE), U8.7 (GND), U9.6 (MODE), U9.7 (GND), X1.2 (GND)
unnamed: C11.1, R6.2, R7.1
unnamed: C15.1, R8.2, R9.1
unnamed: D4.2 (A), D5.2 (A2), J2.2
unnamed: D8.1 (K), R12.1
unnamed: D9.1 (K), R13.1
unnamed: D10.1 (K), R18.1
unnamed: D11.1 (K), R19.1
unnamed: D12.2 (A), R26.2
unnamed: D13.2 (A), R27.2
unnamed: D14.2 (A), R28.2
unnamed: D15.2 (A), R29.2
unnamed: D16.2 (A), R30.2
unnamed: J7.A5 (CC1_A), R14.2
unnamed: J7.B5 (CC2_B), R15.2
unnamed: J8.A5 (CC1_A), R20.2
unnamed: J8.B5 (CC2_B), R21.2
unnamed: J9.A5 (CC1_A), R22.2
unnamed: J9.B5 (CC2_B), R23.2
unnamed: R10.2, U4.9 (USBDM)
unnamed: R11.2, U4.8 (USBDP)
unnamed: C19.1, C20.1, FB1.2, U4.12 (VCC)
unnamed: R16.2, U5.9 (USBDM)
unnamed: R17.2, U5.8 (USBDP)
unnamed: C25.1, C26.1, FB2.2, U5.12 (VCC)
VBUS: C34.1, C37.1, C40.1, C43.1, D1.1 (K), D2.1 (K), D3.1 (K), D4.1 (K), U6.4 (VIN), U6.5 (EN), U7.4 (VIN), U7.5 (EN), U8.4 (VIN), U8.5 (EN), U9.4 (VIN), U9.5 (EN)

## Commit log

2024-10-10 add headers for ACS and sun sensors
2024-10-11 use SAMTEC connectors for AVI to side panels, try HARWIN ones next
2024-10-12 AVI: using through hole M50 connectors for sun detectors and ACS
2024-10-12 EPS use M50 2x3 connectors for solar cells. remove 2 connectors since they are all tied together and top/bottom can be routed through sides and side connectors
2024-10-12 cleanup around watchdog, remove TPs
2024-10-12 inching toward ordering SCI and AUX
2024-10-13 add SPI CS and MISO pullups and terminations, remove WD from SCI
2024-10-13 tweaking SCI and AUX for production, using common sheets as much as possible
2024-10-14 clenup BOM for SCI and AUX
2024-10-15 cleaning up bom: remove main camera port since it has not pullups and capacitors, correcting some errors in camera switch
2024-10-16 QC, add second 3V regulator to AUX, INT pullups on AUX SCI AVI
2024-10-17 propate the changes to RF
2024-10-19 tweaks before merge
2024-10-20 local switches and monitors for SCI and RF
2024-10-21 AVI board manages its local powers
